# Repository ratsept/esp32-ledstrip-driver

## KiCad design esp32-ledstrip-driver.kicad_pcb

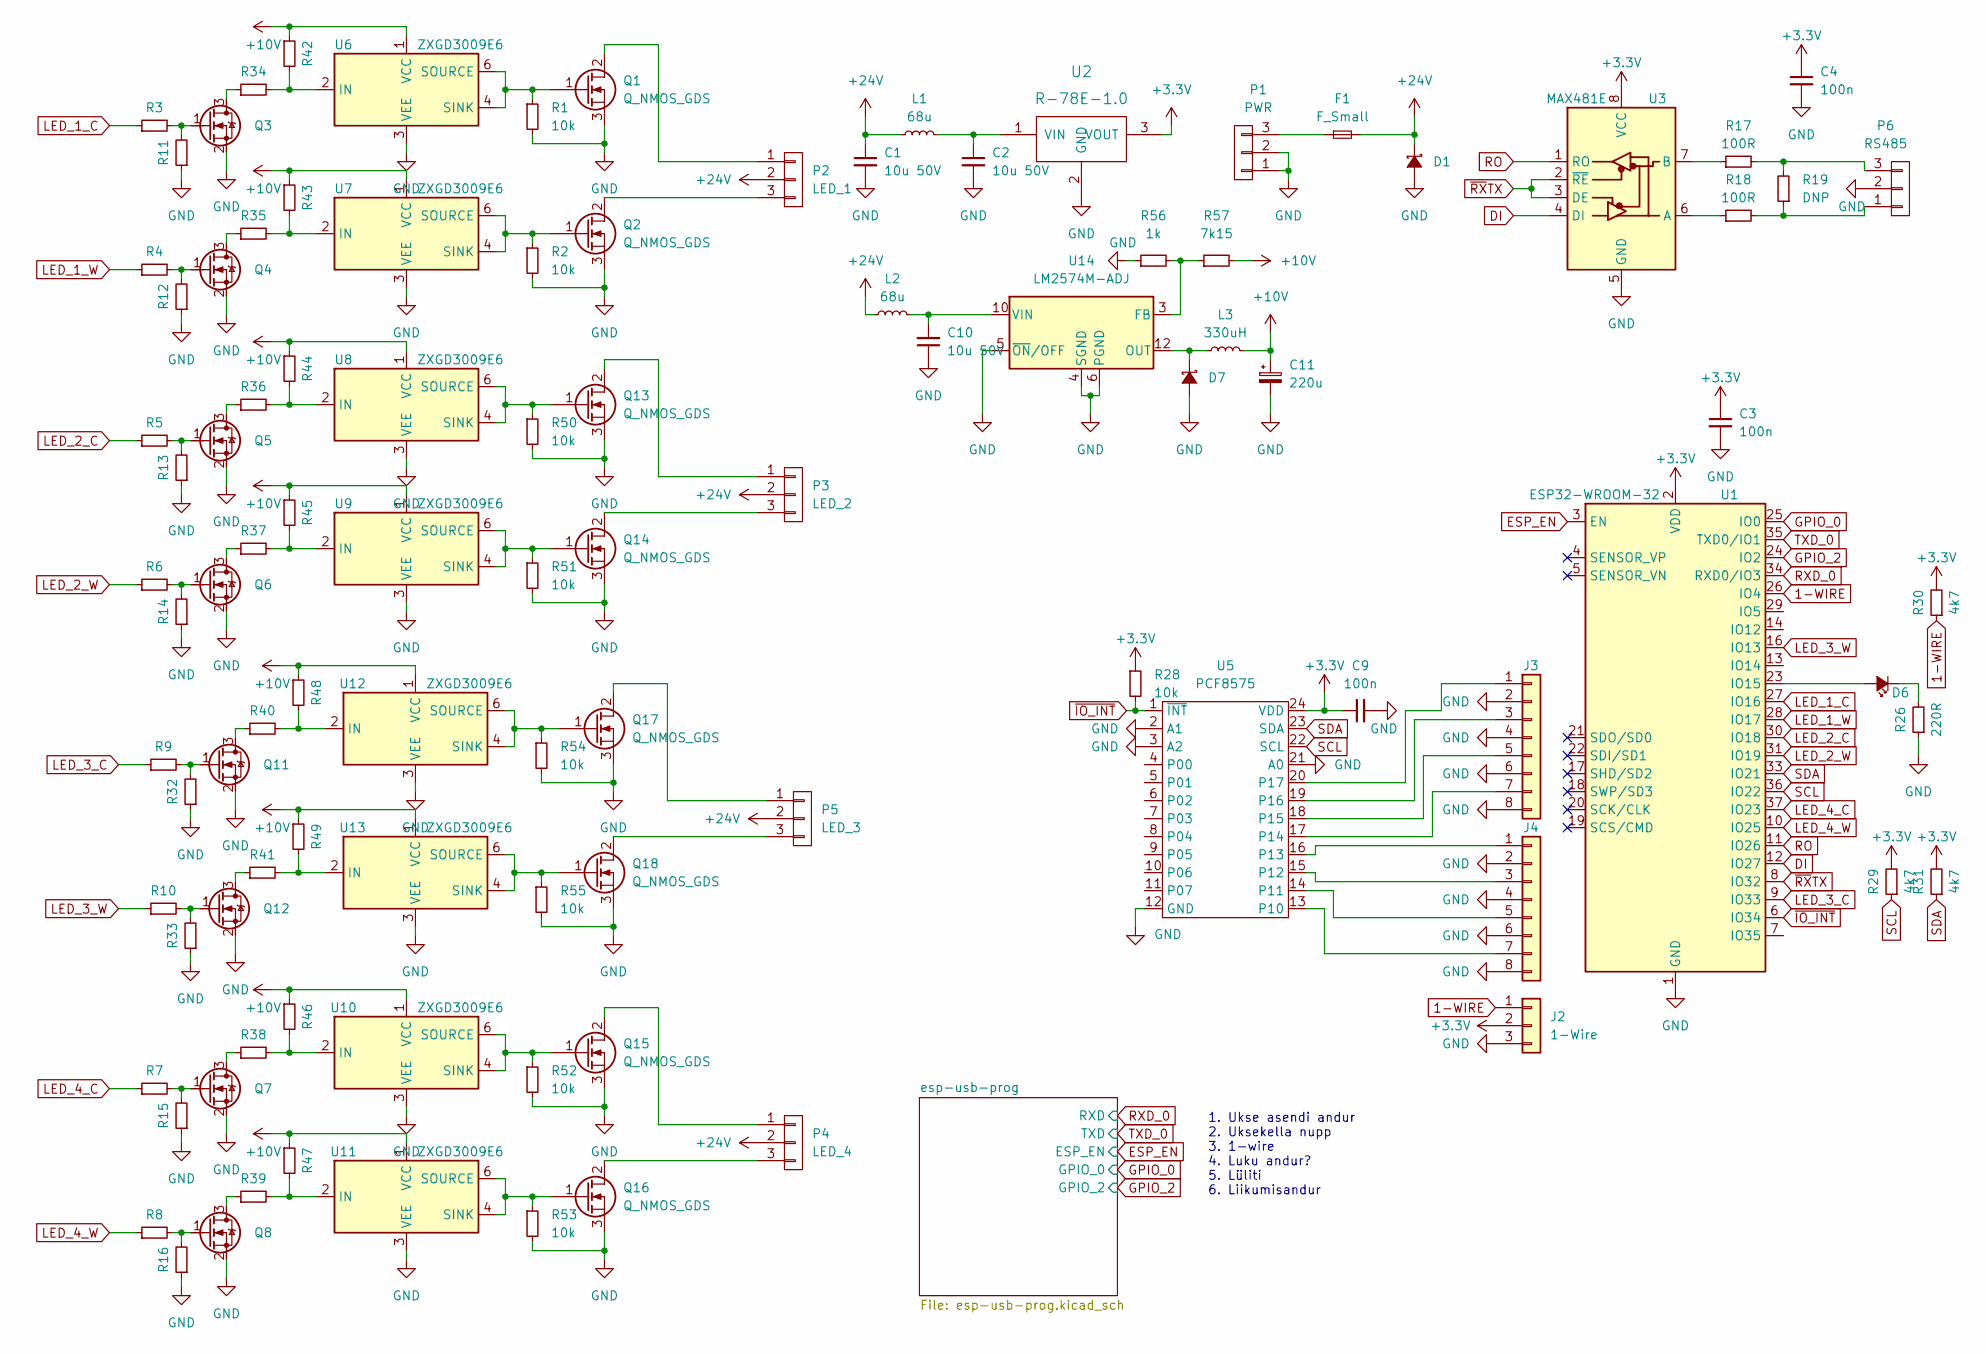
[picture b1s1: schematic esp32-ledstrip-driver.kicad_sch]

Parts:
C1, C2, C10: 10u 50V; C_1210_3225Metric
C3, C4, C9: 100n; C_0603_1608Metric
C11: 220u; CP_Radial_D8.0mm_P3.50mm
D1, D7: D_Schottky_Small; D_SMA
D6: Led_Small; LED_0805_2012Metric_Pad1.15x1.40mm_HandSolder
F1: F_Small; Fuseholder_TR5_Littelfuse_No560_No460
J2: 1-Wire; TerminalBlock_bornier-3_P5.08mm
J3: Conn_01x08; PinHeader_1x08_P2.54mm_Vertical
J4: Conn_01x08; TerminalBlock_Phoenix_MKDS-1,5-8-5.08_1x08_P5.08mm_Horizont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
L1, L2: 68u; L_6.3x6.3_H3
L3: 330uH; L_6.3x6.3_H3
P1: PWR; PhoenixContact_GMSTBA_2,5_3-G-7,62_1x03_P7.62mm_Horizontal
P2: LED_1; PhoenixContact_GMSTBA_2,5_3-G-7,62_1x03_P7.62mm_Horizontal
P3: LED_2; PhoenixContact_GMSTBA_2,5_3-G-7,62_1x03_P7.62mm_Horizontal
P4: LED_4; PhoenixContact_GMSTBA_2,5_3-G-7,62_1x03_P7.62mm_Horizontal
P5: LED_3; PhoenixContact_GMSTBA_2,5_3-G-7,62_1x03_P7.62mm_Horizontal
P6: RS485; PhoenixContact_GMSTBA_2,5_3-G-7,62_1x03_P7.62mm_Horizontal
Q1, Q2, Q13, Q14, Q15, Q16, Q17, Q18: Q_NMOS_GDS; TO-252-2
Q3, Q4, Q5, Q6, Q7, Q8, Q11, Q12: Q_NMOS_GSD_SMALL; SOT-23
R1, R2, R28, R50, R51, R52, R53, R54, R55: 10k; R_0603_1608Metric
R3, R4, R5, R6, R7, R8, R9, R10, R34, R35, R36, R37, R38, R39, R40, R41: 100R; R_0402_1005Metric
R11, R12, R13, R14, R15, R16, R32, R33: 10k; R_0402_1005Metric
R17, R18: 100R; R_0603_1608Metric
R19: DNP; R_0603_1608Metric
R26: 220R; R_0603_1608Metric
R29, R30, R31: 4k7; R_0603_1608Metric
R42, R43, R44, R45, R46, R47, R48, R49: 1k; R_0402_1005Metric
R56: 1k; R_0603_1608Metric
R57: 7k15; R_0603_1608Metric
U1: ESP32-WROOM-32
U2: R-78E-1.0
U3: MAX481E; SO-8_3.9x4.9mm_P1.27mm
U5: PCF8575; SSOP-24_5.3x8.2mm_P0.65mm
U6, U7, U8, U9, U10, U11, U12, U13: ZXGD3009E6; SOT-23-6
U14: LM2574M-ADJ; SOIC-14W_7.5x9mm_P1.27mm

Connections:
1-WIRE: J2.1, R30.1, U1.26 (IO4)
+3V3: C3.1, C4.1, C9.1, J2.2, R28.1, R29.2, R30.2, R31.2, U1.2 (VDD), U2.3 (VOUT), U3.8 (VCC), U5.24 (VDD); also elsewhere on the board
+10V: C11.1, L3.2, R42.1, R43.1, R44.1, R45.1, R46.1, R47.1, R48.1, R49.1, R57.2, U6.1 (VCC), U7.1 (VCC), U8.1 (VCC), U9.1 (VCC), U10.1 (VCC), U11.1 (VCC), U12.1 (VCC), U13.1 (VCC)
+24V: C1.1, D1.1 (K), F1.2, L1.1, L2.1, P2.2, P3.2, P4.2, P5.2
DI: U1.12 (IO27), U3.4 (DI)
ESP_EN: U1.3 (EN); also elsewhere on the board
GND: C1.2, C2.2, C3.2, C4.2, C9.2, C10.1, C11.2, D1.2 (A), D7.2 (A), J2.3, J3.2, J3.4, J3.6, J3.8, J4.2, J4.4, J4.6, J4.8, P1.1, P1.2, P6.2, Q1.3 (S), Q2.3 (S), Q3.2 (S), Q4.2 (S), Q5.2 (S), Q6.2 (S), Q7.2 (S), Q8.2 (S), Q11.2 (S), Q12.2 (S), Q13.3 (S), Q14.3 (S), Q15.3 (S), Q16.3 (S), Q17.3 (S), Q18.3 (S), R1.2, R2.2, R11.1, R12.1, R13.1, R14.1, R15.1, R16.1, R26.1, R32.1, R33.1, R50.2, R51.2, R52.2, R53.2, R54.2, R55.2, R56.1, U1.1 (GND), U1.15 (GND), U1.38 (GND), U1.39 (GND), U2.2 (GND), U3.5 (GND), U5.2 (A1), U5.3 (A2), U5.12 (GND), U5.21 (A0), U6.3 (VEE), U7.3 (VEE), U8.3 (VEE), U9.3 (VEE), U10.3 (VEE), U11.3 (VEE), U12.3 (VEE), U13.3 (VEE), U14.4 (SGND), U14.5 (~ON/OFF), U14.6 (PGND); also elsewhere on the board
GPIO_0: U1.25 (IO0); also elsewhere on the board
GPIO_2: U1.24 (IO2); also elsewhere on the board
LED_1_C: R3.1, U1.27 (IO16)
LED_1_W: R4.1, U1.28 (IO17)
LED_2_C: R5.1, U1.30 (IO18)
LED_2_W: R6.1, U1.31 (IO19)
LED_3_C: R9.1, U1.9 (IO33)
LED_3_W: R10.1, U1.16 (IO13)
LED_4_C: R7.1, U1.37 (IO23)
LED_4_W: R8.1, U1.10 (IO25)
unnamed: C2.1, L1.2, U2.1 (VIN)
unnamed: D6.1 (K), R26.2
unnamed: D6.2 (A), U1.23 (IO15)
unnamed: D7.1 (K), L3.1, U14.12 (OUT)
unnamed: F1.1, P1.3
unnamed: J3.1, U5.20 (P17)
unnamed: J3.3, U5.19 (P16)
unnamed: J3.5, U5.18 (P15)
unnamed: J3.7, U5.17 (P14)
unnamed: J4.1, U5.16 (P13)
unnamed: J4.3, U5.15 (P12)
unnamed: J4.5, U5.14 (P11)
unnamed: J4.7, U5.13 (P10)
unnamed: C10.2, L2.2, U14.10 (VIN)
unnamed: P2.1, Q1.2 (D)
unnamed: P2.3, Q2.2 (D)
unnamed: P3.1, Q13.2 (D)
unnamed: P3.3, Q14.2 (D)
unnamed: P4.1, Q15.2 (D)
unnamed: P4.3, Q16.2 (D)
unnamed: P5.1, Q17.2 (D)
unnamed: P5.3, Q18.2 (D)
unnamed: P6.1, R18.2, R19.1
unnamed: P6.3, R17.2, R19.2
unnamed: Q1.1 (G), R1.1, U6.4 (SINK), U6.6 (SOURCE)
unnamed: Q2.1 (G), R2.1, U7.4 (SINK), U7.6 (SOURCE)
unnamed: Q3.1 (G), R3.2, R11.2
unnamed: Q3.3 (D), R34.1
unnamed: Q4.1 (G), R4.2, R12.2
unnamed: Q4.3 (D), R35.1
unnamed: Q5.1 (G), R5.2, R13.2
unnamed: Q5.3 (D), R36.1
unnamed: Q6.1 (G), R6.2, R14.2
unnamed: Q6.3 (D), R37.1
unnamed: Q7.1 (G), R7.2, R15.2
unnamed: Q7.3 (D), R38.1
unnamed: Q8.1 (G), R8.2, R16.2
unnamed: Q8.3 (D), R39.1
unnamed: Q11.1 (G), R9.2, R32.2
unnamed: Q11.3 (D), R40.1
unnamed: Q12.1 (G), R10.2, R33.2
unnamed: Q12.3 (D), R41.1
unnamed: Q13.1 (G), R50.1, U8.4 (SINK), U8.6 (SOURCE)
unnamed: Q14.1 (G), R51.1, U9.4 (SINK), U9.6 (SOURCE)
unnamed: Q15.1 (G), R52.1, U10.4 (SINK), U10.6 (SOURCE)
unnamed: Q16.1 (G), R53.1, U11.4 (SINK), U11.6 (SOURCE)
unnamed: Q17.1 (G), R54.1, U12.4 (SINK), U12.6 (SOURCE)
unnamed: Q18.1 (G), R55.1, U13.4 (SINK), U13.6 (SOURCE)
unnamed: R17.1, U3.7 (B)
unnamed: R18.1, U3.6 (A)
unnamed: R34.2, R42.2, U6.2 (IN)
unnamed: R35.2, R43.2, U7.2 (IN)
unnamed: R36.2, R44.2, U8.2 (IN)
unnamed: R37.2, R45.2, U9.2 (IN)
unnamed: R38.2, R46.2, U10.2 (IN)
unnamed: R39.2, R47.2, U11.2 (IN)
unnamed: R40.2, R48.2, U12.2 (IN)
unnamed: R41.2, R49.2, U13.2 (IN)
unnamed: R56.2, R57.1, U14.3 (FB)
RO: U1.11 (IO26), U3.1 (RO)
RXD_0: U1.34 (RXD0/IO3); also elsewhere on the board
SCL: R29.1, U1.36 (IO22), U5.22 (SCL)
SDA: R31.1, U1.33 (IO21), U5.23 (SDA)
TXD_0: U1.35 (TXD0/IO1); also elsewhere on the board
~IO_INT: R28.2, U1.6 (IO34), U5.1 (~INT)
~RXTX: U1.8 (IO32), U3.2 (~RE), U3.3 (DE)

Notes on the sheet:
1. Ukse asendi andur 2. Uksekella nupp 3. 1-wire 4. Luku andur? 5. Lüliti 6. Liikumisandur

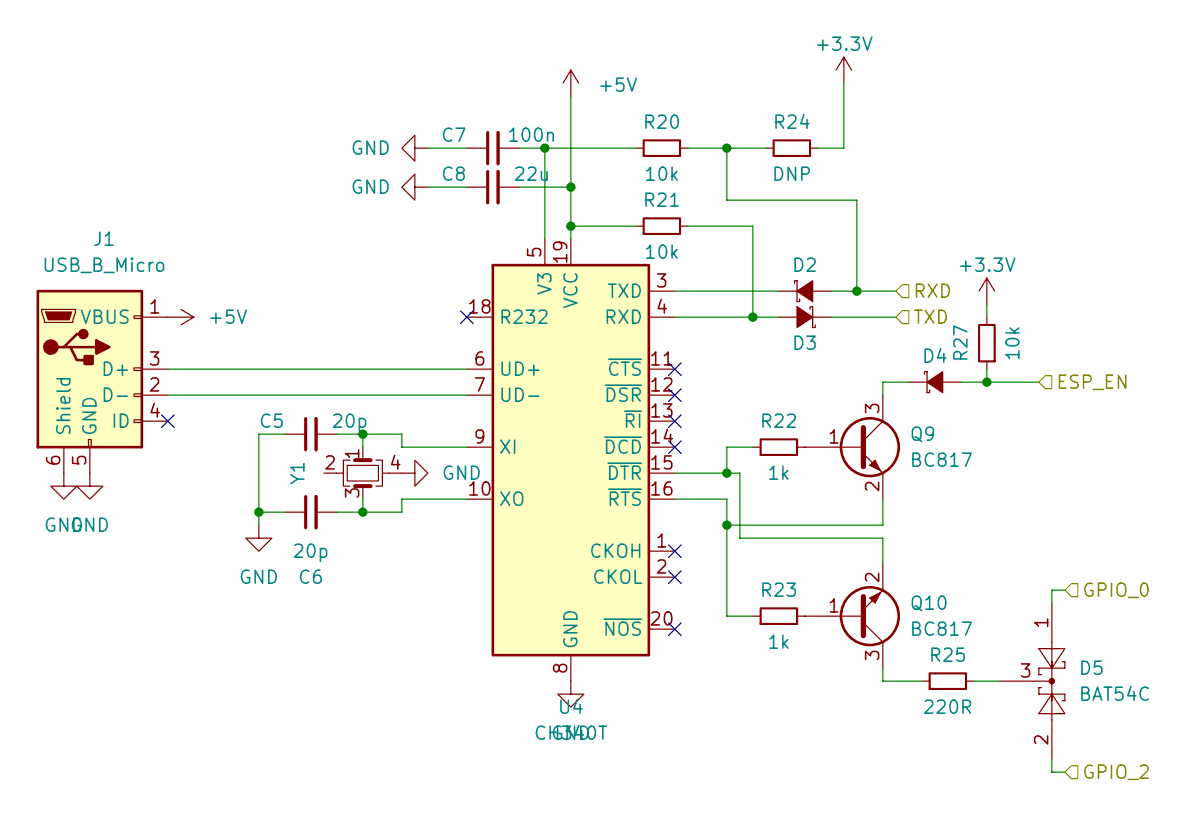
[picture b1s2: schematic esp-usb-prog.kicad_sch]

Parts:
C5, C6: 20p; C_0603_1608Metric
C7: 100n; C_0603_1608Metric
C8: 22u; C_0603_1608Metric
D2, D3, D4: D_Schottky_Small; D_0603_1608Metric_Pad1.05x0.95mm_HandSolder
D5: BAT54C; SOT-23
J1: USB_B_Micro; USB_Mini-B_Tensility_54-00023_Vertical_CircularHoles
Q9, Q10: BC817; SOT-23
R20, R21, R27: 10k; R_0603_1608Metric
R22, R23: 1k; R_0603_1608Metric
R24: DNP; R_0603_1608Metric
R25: 220R; R_0603_1608Metric
U4: CH340T; SSOP-20_5.3x7.2mm_P0.65mm
Y1: Crystal_GND24_Small; Crystal_SMD_3225-4Pin_3.2x2.5mm_HandSoldering; MPN ABM8G-106-12.000MHZ-T

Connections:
+3V3: R24.2, R27.2; also elsewhere on the board
+5V: C8.2, J1.1 (VBUS), R21.1, U4.19 (VCC)
ESP_EN: D4.2 (A), R27.1; also elsewhere on the board
GND: C5.1, C6.1, C7.1, C8.1, J1.5 (GND), J1.6 (Shield), U4.8 (GND), Y1.4; also elsewhere on the board
GPIO_0: D5.1; also elsewhere on the board
GPIO_2: D5.2; also elsewhere on the board
unnamed: C5.2, U4.9 (XI), Y1.1
unnamed: C6.2, U4.10 (XO), Y1.3
unnamed: C7.2, R20.1, U4.5 (V3)
unnamed: D2.1 (K), U4.3 (TXD)
unnamed: D3.2 (A), R21.2, U4.4 (RXD)
unnamed: D4.1 (K), Q9.3 (C)
unnamed: D5.3, R25.2
unnamed: J1.2 (D-), U4.7 (UD-)
unnamed: J1.3 (D+), U4.6 (UD+)
unnamed: Q9.1 (B), R22.2
unnamed: Q9.2 (E), R23.1, U4.16 (~RTS)
unnamed: Q10.1 (B), R23.2
unnamed: Q10.2 (E), R22.1, U4.15 (~DTR)
unnamed: Q10.3 (C), R25.1
RXD_0: D2.2 (A), R20.2, R24.1; also elsewhere on the board
TXD_0: D3.1 (K); also elsewhere on the board

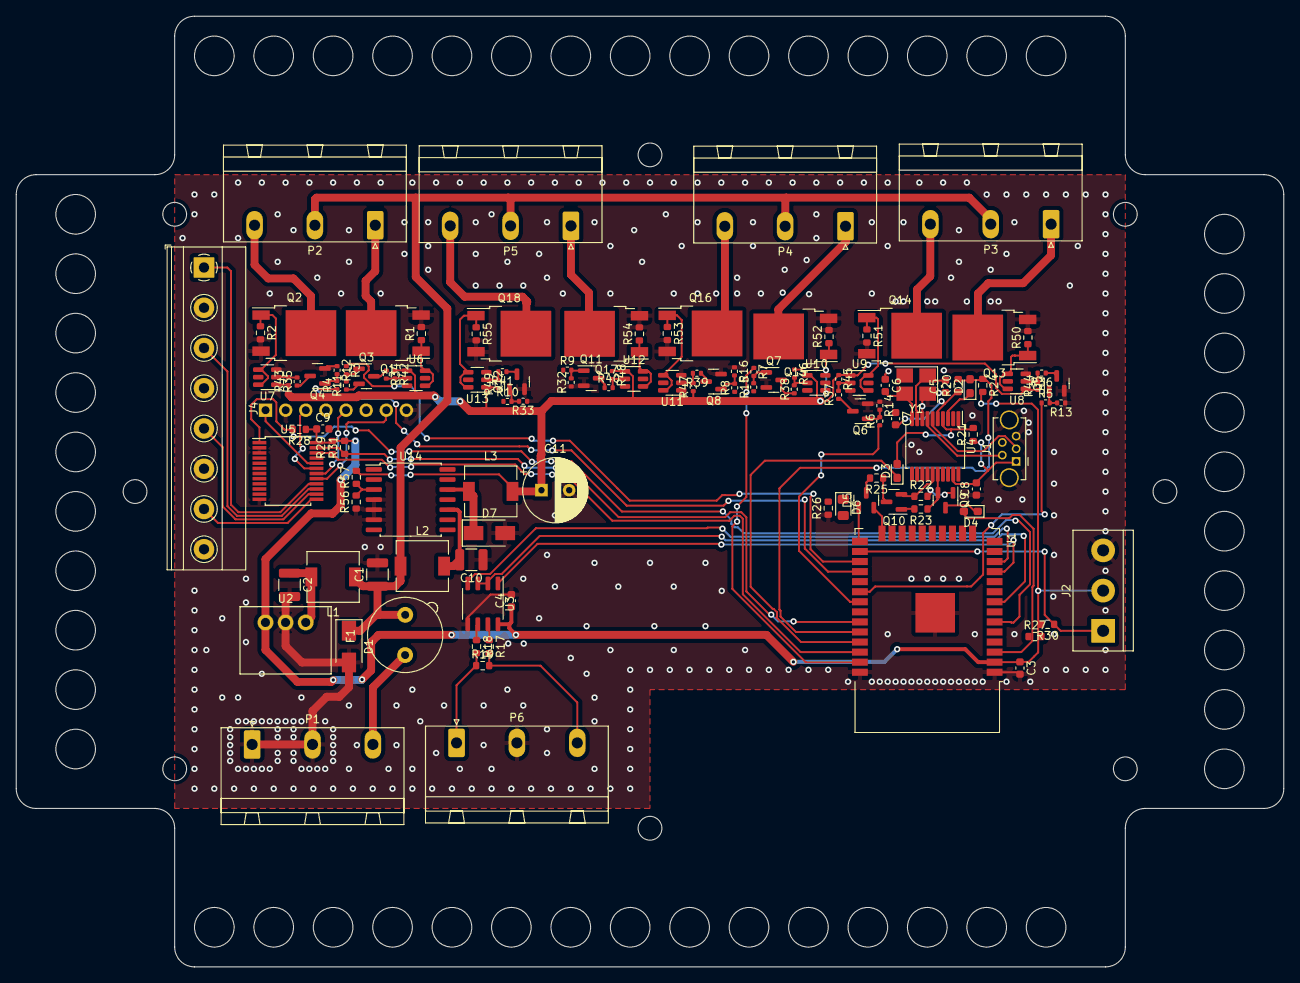
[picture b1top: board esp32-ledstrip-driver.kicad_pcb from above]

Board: 2 copper layers, 160.0 x 120.0 mm, 122 parts (1 on the bottom side), 98 nets.

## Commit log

2022-02-21 first gerbers generated
2022-02-21 generated gerber archive
2022-04-20 Fixed FET footprints
2024-03-05 Moved Kicad files to electronics folder
2024-03-05 Added Arduino test code
2024-03-05 Removed moved files
